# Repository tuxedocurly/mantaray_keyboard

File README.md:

# Mantaray -  A ZSA Voyager Inspired Ergonomic Mechanical Keyboard
*The Mantaray2040 is a ZSA Voyager inspired low-profile, ortholinear, column staggered ergonomic mechanical keyboard. The design is intended to provide a low-cost, easy to build alternative to the ZSA Voyager for users who aren't looking for a split keyboard design.*

Keyboard Creator and Maintainer: [Colton Hawkins AKA TuxedoMakes](https://youtube.com/@TuxedoMakes)

*Key features:*
- PCB is compatible with any pro-micro board
- 128x32 vertical OLED
- USB-C
- Kailh choc v1 switch compatible
- Ultra thin, ultra portable

##  Support This Project (and Fuel Open Source!)

This project is a labor of love, built during my spare time. If you've found this keyboard design helpful, interesting, or just plain awesome, consider checking out [my shop](https://ko-fi.com/tuxedomakes/shop) where I sell PCBs and parts to make my projects, or buy me a coffee!

**Your support helps me:**

*   Dedicate more time to improve this design.
*   Experiment with new features and ideas.
*   Kickstart other open-source projects that you might love.

Even a small coffee-sized contribution goes a long way in fueling my passion for open source. If you use the shop, you'll get a useful part for your next project, plus my eternal gratitude!

**Thank you for being awesome!**

## Build Guide
*Video guide available on my [YouTube channel](https://www.youtube.com/@TuxedoMakes).*
* Supported Controllers: *Anything pro-micro pin compatible. The provided firmware has been built for an RP2040-based pro-micro compatible controller.*
* Hardware Needed:
  - 1 x Mantaray PCB
  - 1 x RP2040 Pro Micro Controller ([Amazon](https://amzn.to/428M2m1), [AliExpress](https://www.aliexpress.us/item/3256806600745653.html))
  - 52 x Kailh Hotswap Sockets ([Amazon](https://amzn.to/4h6iSsb))
  - 52 x Kailh Choc V1 Switches ([Amazon](https://amzn.to/4fRsSVb))
  - 52 x Kailh choc v1 compatible keycaps ([Amazon](https://amzn.to/4ae0R8R))
  - 52 x 1N4148 through-hole Diodes ([Amazon](https://amzn.to/40qinUf))
    - Alternatively, you can use surface mount diodes ([Amazon](https://amzn.to/3WbPPeA))
  - 1 x 128x32 SSD1306 OLED Display ([Amazon](https://amzn.to/3Wcarnd))
  - 1 x 3D printed case (STL files available in this repo, or via [MakerWorld](https://makerworld.com/en/models/972433#profileId-944453))
  - 8 x M2x5mm tapered head machine screws ([Amazon](https://amzn.to/3BTecHg))
  - Optional Stuff
    - 1 x Reset Button ([Amazon](https://amzn.to/3Pt3eer))
    - 1 x Syringe of Solder Flux ([Amazon](https://amzn.to/4fXnPT4))
    - 8 x M2x3x3.2mm Heat Set Inserts ([Amazon](https://amzn.to/40bUWMX))
      - While the inserts are technically optional, I highly recommend using them. They're awesome.

**Step 1: Solder Diodes**

Solder all the through hole or surface-mount diodes to the board. Note the direction of the diodes carefully, as they have a polarity (the black stripe should face the square contact on the PCB).

If you decide to use through-hole diodes like I did, be sure to solder the diodes from the  back side of the PCB to avoid globs of solder forming on the front side - the front of the PCB needs to be flat in order for the choc switches to sit flush when installed later.Also, be sure to trim the excess wire from the other side of the board to keep things as tidy and low-profile as possible. A good pair of nippers comes in handy here.

This is how the diodes should look after soldering

This is how the front of the board should look after snipping off the excess diode legs to make them flush with the PCB.

**Step 2: Solder Hotswap Sockets**

Next, go ahead and place the hotswap sockets on the board and solder them in. This step is slightly tedious, but pretty straight forward.

Here's how the back of the PCB should look once the hotswap sockets are installed.

**Step 3: Solder Controller to PCB**

Keeping everything low profile is very important here, so I used a mid-mount USB C RP2040 pro micro board. The provided case file is designed to work with this type of controller, and you *may* run into clearance issues if you use a standard top-mounted USB C pro micro.

With that out of the way, follow bakingpy's [guide](https://imgur.com/a/how-to-solder-pro-micro-header-pins-like-badass-M9r3EW9) to get the headers for the controller soldered to the PCB. TL;DR - solder the pin headers in to the bottom of the board, making sure they don't protrude from the front of the board. Once they're all soldered, remove the plastic spacer piece using some tweezers.

Once that's done, install the RP2040 Pro Micro on the bottom side of the keyboard PCB. The IC and reset buttons should be facing away from the PCB, allowing the microcontroller to sit nearly flush with the PCB. Trim the excess wire from the pin headers, and you're done with this step.

Here's how the final result should look:

**Step 4: Solder OLED Display**

Time to install the display. Grab the 128x32 SSD1306 OLED and install it into the front of the pcb. The process is very similar to installing the controller to the PCB, but luckily we only have to deal with 4 pins this time. Follow bakingpy's [guide](https://imgur.com/a/how-to-solder-pro-micro-header-pins-like-badass-M9r3EW9) to install the 4 pin headers onto the front of the PCB, then add the OLED onto the headers and solder it into place. **Be sure to solder this as straight as posible, using the silkscreen lines on the front of the PCB as reference**. The display needs to be relatively straight in order to fit into its cutout in the top case later.

Here's how the display should look just before soldering it to the headers.

**Step 5: (Optional) Install Front Reset Button**

Because the controller I chose has a reset button built into the board, and I built access to the button into the back of the 3D printed case, this step is not required; however, it is recommended as it makes accessing the bootloader a bit easier.

If you decide to add the reset button, there isn't much to say here. Grab a [reset button](https://amzn.to/3Pt3eer), and solder it onto the PCB. A bit of [flux](https://amzn.to/4fXnPT4) is extremely helpful here.

See the image above for a reference of the reset button install location.

**Step 6: The Case**

Print yourself a case using the files in this repo, or by grabbing them on [MakerWorld](https://makerworld.com/en/models/972433#profileId-944453).

Install the heat set inserts into each of the posts with holes on the bottom plate. Note that there are 4 posts that do not have holes for inserts. Those are supports for the PCB, and can be ignored.

Screw the PCB into the case using 8 x M2x5mm tapered head machine screws.

Place the top case over the PCB. Pay attention to the cutout for the OLED display, and make sure you soldered this straight enough to fit into the cutout. If needed, go back and reflow the solder to better align the display. You're almost done - hang in there!

**Step 7: Install Switches and Keycaps**

Grab your Kailh Choc V1 switches and install them over the plate, into the hotswap sockets on the pcb. Watch for bent pins. Once all the switches are installed, go ahead and add your keycaps.

**Step 8: Install the Firmware**

Hold down the reset button as you plug the keyboard into your computer. Release the reset button once the board is plugged in, and you should see a removable drive appear with the name "RPI-RP2". If this doesn't work, try plugging in the keyboard, then double tapping the reset button. Download the mantaray2040_default.u2f firmware file from this repo, then drag and drop it into the removable drive that appeared.

The keyboard should reboot, and the firmware should now be flashed! Enjoy your new ergonomic keyboard!

## Firmware
There are two options for getting the firmware file:
1. download the pre-build firmware file from this repository (mantaray2040_default.u2f)
2. build the firmware yourself from the source provided in this repository

**How to build the firmware (after setting up the build environment):**
1. Set up your build environment according to the QMK documentation for your OS

2. Clone the mantaray2040 repo, unzip the file, and add it to you qmk_firmware/keyboards folder

3. Run the build command. Below is an example for linux:

    qmk compile -kb mantaray2040 -km default

4. You  should now have a firmware file named mantaray2040_default.uf2 in the qmk_firmware directory (or the output directory you specified).

**How to flash the firmware:**
1. Download the mantaray2040_default.u2f firmware file, or compile the firmware yourself.
1. Enter the bootloader by plugging in your mantaray2040 and double tapping the "reset" button.
2. A removable drive should appear named "RPI-RP2" or similar.
3. Drag and drop the mantaray2040_default.u2f firmware file onto the "RPI-RP2" removable drive.
4. Your keyboard should now be flashed and ready to use.

See the [build environment setup](https://docs.qmk.fm/#/getting_started_build_tools) and the [make instructions](https://docs.qmk.fm/#/getting_started_make_guide) for more information. Brand new to QMK? Start with the [Complete Newbs Guide](https://docs.qmk.fm/#/newbs).

## Bootloader

Enter the bootloader in 2 ways:

* **Physical reset button**: Double tap the "Reset" button located on your microcontroller. Alternatively, if you've installed the optional reset button on the front of the PCB, double tap that.
* **Keycode in layout**: Press the key mapped to `QK_BOOT` (top right key on layer 2)

## LICENSE
As per QMK's licensing requirements, the firmware for the Mantaray keyboard is released under GPLv3. Hardware design files, including electronics and mechanical files, are released under OHL CERN v2-S. Check the respective directories for full license text.

## ❤️ Support Me ❤️

If you liked this project, please consider checking out [my shop](https://ko-fi.com/tuxedomakes/shop) or [buying me a coffee ☕](https://ko-fi.com/tuxedomakes).

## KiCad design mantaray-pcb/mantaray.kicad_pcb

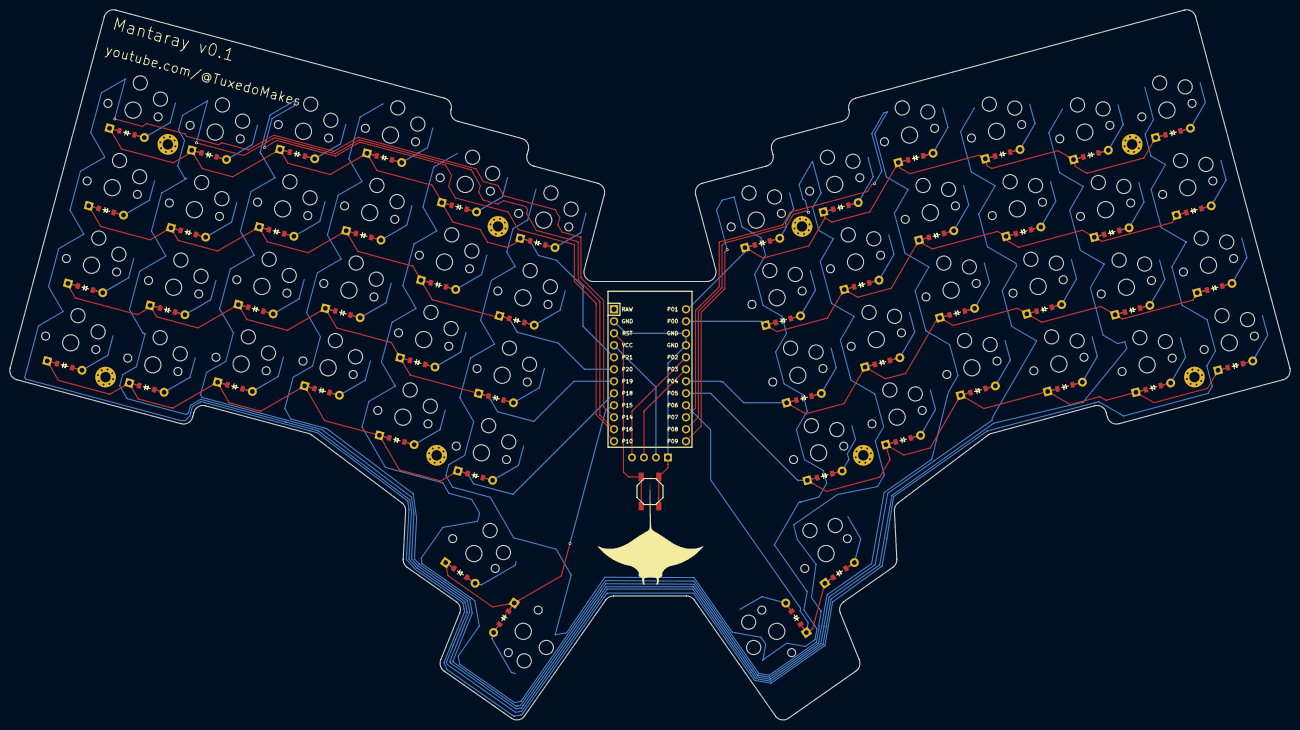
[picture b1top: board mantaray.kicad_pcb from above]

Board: 2 copper layers, 271.1 x 150.3 mm, 115 parts (0 on the bottom side), 73 nets.

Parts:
B1: SW_TACT_ALPS_SKQGABE010
D1, D2, D3, D4, D5, D6, D7, D8, D9, D10, D11, D12, D13, D14, D15, D16, D17, D18, D19, D20, D21, D22, D23, D24, D25, D26, D27, D28, D29, D30, D31, D32, D33, D34, D35, D36, D37, D38, D39, D40, D41, D42, D43, D44, D45, D46, D47, D48, D49, D50, D51, D52: ComboDiode
MCU1: ProMicro
OLED1: OLED; OLED_headers
S1, S2, S3, S4, S5, S6, S7, S8, S9, S10, S11, S12, S13, S14, S15, S16, S17, S18, S19, S20, S21, S22, S23, S24, S25, S26, S27, S28, S29, S30, S31, S32, S33, S34, S35, S36, S37, S38, S39, S40, S41, S42, S43, S44, S45, S46, S47, S48, S49, S50, S51, S52: PG1350
_1, _2, _3, _4, _5, _6, _7, _8: MountingHole_2.2mm_M2_Pad_Via

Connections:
GND: B1.1, MCU1.2, MCU1.15, MCU1.16, OLED1.1
P0: D29.1, D33.1, D37.1, D41.1, D45.1, D49.1, MCU1.14
P1: D30.1, D34.1, D38.1, D42.1, D46.1, D50.1, MCU1.13
P2: MCU1.17, OLED1.4
P3: MCU1.18, OLED1.3
P4: D28.1, D32.1, D36.1, D40.1, D44.1, D48.1, MCU1.19
P5: D27.1, D31.1, D35.1, D39.1, D43.1, D47.1, MCU1.20
P6: D51.1, D52.1, MCU1.21
P7: MCU1.22, S13.1, S14.1, S15.1, S16.1, S39.1, S40.1, S41.1, S42.1
P8: MCU1.23, S17.1, S18.1, S19.1, S20.1, S25.1, S43.1, S44.1, S45.1, S46.1, S51.1
P9: MCU1.24, S21.1, S22.1, S23.1, S24.1, S26.1, S47.1, S48.1, S49.1, S50.1, S52.1
P10: MCU1.12, S9.1, S10.1, S11.1, S12.1, S35.1, S36.1, S37.1, S38.1
P14: MCU1.10, S1.1, S2.1, S3.1, S4.1, S27.1, S28.1, S29.1, S30.1
P15: D25.1, D26.1, MCU1.9
P16: MCU1.11, S5.1, S6.1, S7.1, S8.1, S31.1, S32.1, S33.1, S34.1
P18: D1.1, D5.1, D9.1, D13.1, D17.1, D21.1, MCU1.8
P19: D2.1, D6.1, D10.1, D14.1, D18.1, D22.1, MCU1.7
P20: D3.1, D7.1, D11.1, D15.1, D19.1, D23.1, MCU1.6
P21: D4.1, D8.1, D12.1, D16.1, D20.1, D24.1, MCU1.5
RST: B1.2, MCU1.3
VCC: MCU1.4, OLED1.2
index_bottom: D17.2, S17.2
index_home: D18.2, S18.2
index_num: D20.2, S20.2
index_top: D19.2, S19.2
inner_bottom: D21.2, S21.2
inner_home: D22.2, S22.2
inner_num: D24.2, S24.2
inner_top: D23.2, S23.2
layer_cluster: D25.2, S25.2
middle_bottom: D13.2, S13.2
middle_home: D14.2, S14.2
middle_num: D16.2, S16.2
middle_top: D15.2, S15.2
mirror_index_bottom: D43.2, S43.2
mirror_index_home: D44.2, S44.2
mirror_index_num: D46.2, S46.2
mirror_index_top: D45.2, S45.2
mirror_inner_bottom: D47.2, S47.2
mirror_inner_home: D48.2, S48.2
mirror_inner_num: D50.2, S50.2
mirror_inner_top: D49.2, S49.2
mirror_layer_cluster: D51.2, S51.2
mirror_middle_bottom: D39.2, S39.2
mirror_middle_home: D40.2, S40.2
mirror_middle_num: D42.2, S42.2
mirror_middle_top: D41.2, S41.2
mirror_outer_bottom: D27.2, S27.2
mirror_outer_home: D28.2, S28.2
mirror_outer_num: D30.2, S30.2
mirror_outer_top: D29.2, S29.2
mirror_pinky_bottom: D31.2, S31.2
mirror_pinky_home: D32.2, S32.2
mirror_pinky_num: D34.2, S34.2
mirror_pinky_top: D33.2, S33.2
mirror_ring_bottom: D35.2, S35.2
mirror_ring_home: D36.2, S36.2
mirror_ring_num: D38.2, S38.2
mirror_ring_top: D37.2, S37.2
mirror_space_cluster: D52.2, S52.2
outer_bottom: D1.2, S1.2
outer_home: D2.2, S2.2
outer_num: D4.2, S4.2
outer_top: D3.2, S3.2
pinky_bottom: D5.2, S5.2
pinky_home: D6.2, S6.2
pinky_num: D8.2, S8.2
pinky_top: D7.2, S7.2
ring_bottom: D9.2, S9.2
ring_home: D10.2, S10.2
ring_num: D12.2, S12.2
ring_top: D11.2, S11.2
space_cluster: D26.2, S26.2

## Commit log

2025-01-02 Create README.md
    Initial commit of README.md template
2025-01-02 Create README.md for mantaray-pcb
    initial commit
2025-01-02 Add mantaray KiCAD PCB design files
    The (currently untested) mantaray rev 0.1 PCB design files
2025-01-02 Create README.md for firmware
    Initial commit
2025-01-02 Upload keyboard.json config
    Initial commit of WIP mantaray keyboard.json config for qmk
2025-01-08 Update keyboard.json with full keymap and feature set
    Added all keys to the layout matrix.
2025-01-08 Create keymap.c
    Initial commit of base keymap
2025-01-08 Update keyboard.json with v1 config
    Update the config to match the "final" layout macro. Also updated the board URL
2025-01-08 Update rules.mk to remove OLED_ENABLE
    Remove OLED_ENABLE from the rules.mk file.
    Enabling the OLED feature can be done via keyboard.json and/or the rules.mk file. The multiple declarations are redundant, and to keep the configs clean, the declaration in rules.mk has been removed.
2025-01-08 Update keymap.c to include full keymap and layers
    Add all layers to keymap and add OLED display functionality.
    The keymap and layers have been updated to mimic the default layout for the ZSA Voyager.
    Additionally, oled_task_user() has been updated to include the current caps lock state, current layer state, and current estimated WPM count.
2025-01-08 Update config.h to include TAPPING_TERM
    Add TAPPING_TERM definition to config.h.
    TAPPING_TERM defines the amount of time in MS that a "tap" is considered to be a "hold". This affects how long it takes for a key with multiple functions to recognize the "hold" bound function. The d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
2025-01-09 Update keymap.c CW_TOGG to KC_CAPS
    Change CW_TOGG to KC_CAPS.
    Turns out, I don't prefer using caps word over caps lock, so changing this back to something I find to be a more sensible default.
2025-01-09 Update README.md
    Add info for the Mantaray to the readme template.
2025-01-09 Update README.md
    Add more details to build instructions.
2025-01-10 Add case files
    Add mantaray case files (.3mf and .stl)
2025-01-10 Added fusion360 archive files
    Add .f3d files for switch plate and base.
2025-01-10 Create config.yml
    Add ergogen config.yml
    This config.yml is the basis of the PCB design for this project. Start here if you're looking to make major modifications to the PCB and don't want to make those in KiCAD directly.
2025-01-10 Upload gerber zip file
    Add zipped gerber files to make ordering a PCB easier.
    As a user, you can upload the zip file to a PCB manufacturer and order a PCB. I use JLCPCB, and all of the default options work great.
2025-01-10 Upload firmware file for RP2040
    Adding pre-built firmware file for the Mantaray. This can be used as is, and closely aligns with the keymap of the ZSA Voyager
2025-01-10 Update README.md
    corrected spelling
2025-01-16 Update README.md
    Imgur randomly deleted the hosted images. Hosting images here on github instead.
2025-01-16 Update README.md
    Fixed a few broken links
2025-02-18 Add VIAL support
2025-02-18 Add VIAL firmware
2025-07-03 Update README.md
    update buymeacoffee links to ko-fi links
2025-07-17 Update README.md
    Change description to accurately reflect the control board used.
2025-07-30 Update LICENSE
2025-07-30 Update README.md
    Added information about licensing
